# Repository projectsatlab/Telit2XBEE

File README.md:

# Telit2XBEE
XBEE form factor for Telit Sigfox and ZigBee module

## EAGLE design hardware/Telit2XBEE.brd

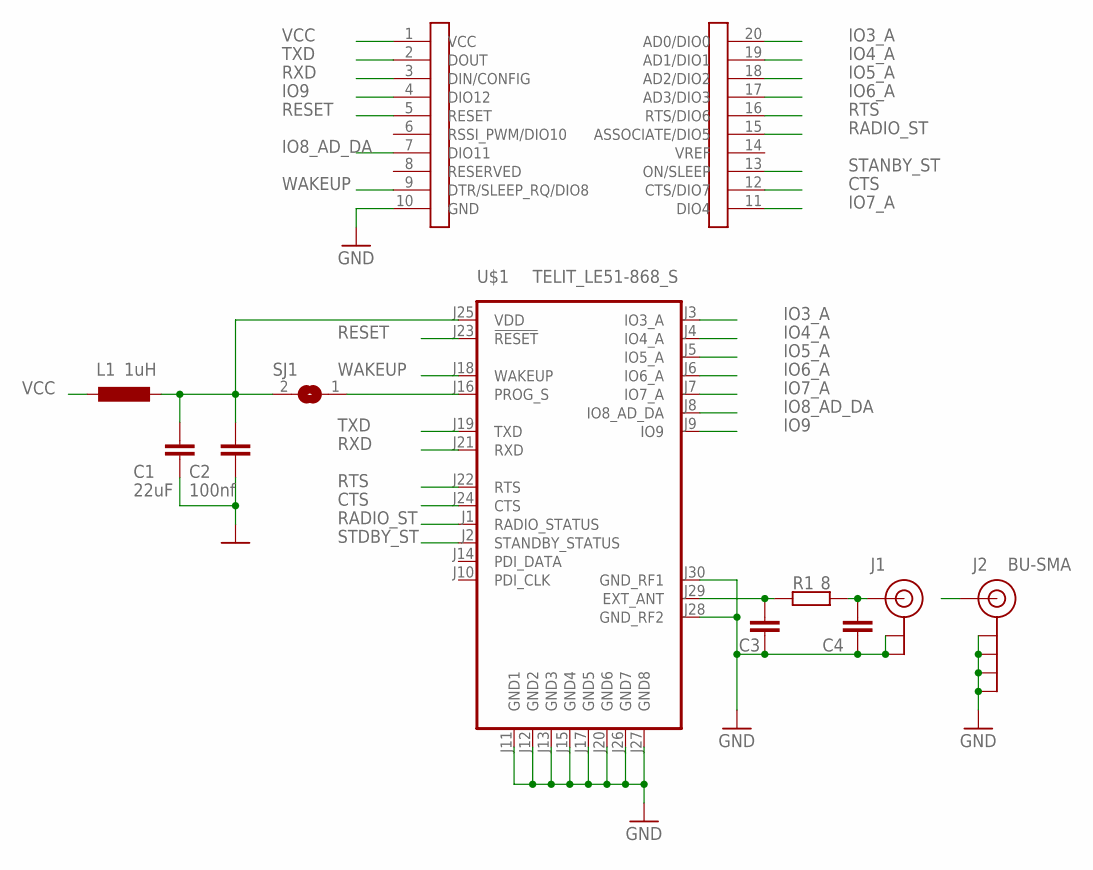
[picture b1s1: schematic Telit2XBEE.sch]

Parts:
C1: 22uF; C1206
C2: 100nf; C0805
C3, C4: C-EUC0201; C0201
J1: U.FL; U.FL_1PAD
J2: BU-SMA; BU-SMA-G
L1: 1uH; COILCRAFT_LPS3015
R1: 8; R0201
SJ1: SJ
U$1: TELIT_LE51-868_S; TELIT_LE51
U$2: XBEE_PIN_HEADER

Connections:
CTS: U$1.J24 (CTS), U$2.12 (CTS/DIO7)
GND: C1.2, C2.2, C3.2, C4.2, J1.P$1 (GND), J1.P$2 (GND), J2.P$2 (GND), J2.P$3 (GND), J2.P$5 (GND), J2.P$6 (GND), U$1.J11 (GND1), U$1.J12 (GND2), U$1.J13 (GND3), U$1.J15 (GND4), U$1.J17 (GND5), U$1.J20 (GND6), U$1.J26 (GND7), U$1.J27 (GND8), U$1.J28 (GND_RF2), U$1.J30 (GND_RF1), U$2.10 (GND)
IO3_A: U$1.J3 (IO3_A), U$2.20 (AD0/DIO0)
IO4_A: U$1.J4 (IO4_A), U$2.19 (AD1/DIO1)
IO5_A: U$1.J5 (IO5_A), U$2.18 (AD2/DIO2)
IO6_A: U$1.J6 (IO6_A), U$2.17 (AD3/DIO3)
IO7_A: U$1.J7 (IO7_A), U$2.11 (DIO4)
IO8_AD_DA: U$1.J8 (IO8_AD_DA), U$2.7 (DIO11)
IO9: U$1.J9 (IO9), U$2.4 (DIO12)
unnamed: SJ1.1, U$1.J16 (PROG_S)
unnamed: C4.1, J1.P$3 (SIGNAL), J2.P$1 (SIGNAL), R1.2
unnamed: C3.1, R1.1, U$1.J29 (EXT_ANT)
unnamed: C1.1, C2.1, L1.P$2 (2), SJ1.2, U$1.J25 (VDD)
RADIO_ST: U$1.J1 (RADIO_STATUS), U$2.15 (ASSOCIATE/DIO5)
RESET: U$1.J23 (!RESET), U$2.5 (RESET)
RTS: U$1.J22 (RTS), U$2.16 (RTS/DIO6)
RXD: U$1.J21 (RXD), U$2.3 (DIN/CONFIG)
STANBY_ST: U$2.13 (ON/SLEEP)
STDBY_ST: U$1.J2 (STANDBY_STATUS)
TXD: U$1.J19 (TXD), U$2.2 (DOUT)
VCC: L1.P$1 (1), U$2.1 (VCC)
WAKEUP: U$1.J18 (WAKEUP), U$2.9 (DTR/SLEEP_RQ/DIO8)

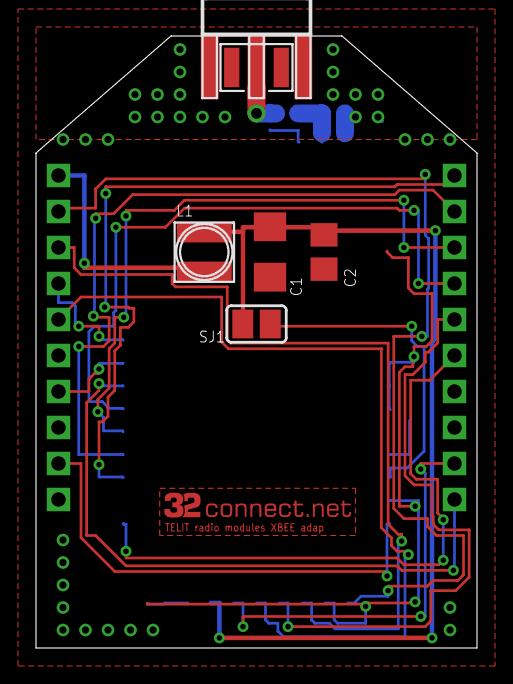
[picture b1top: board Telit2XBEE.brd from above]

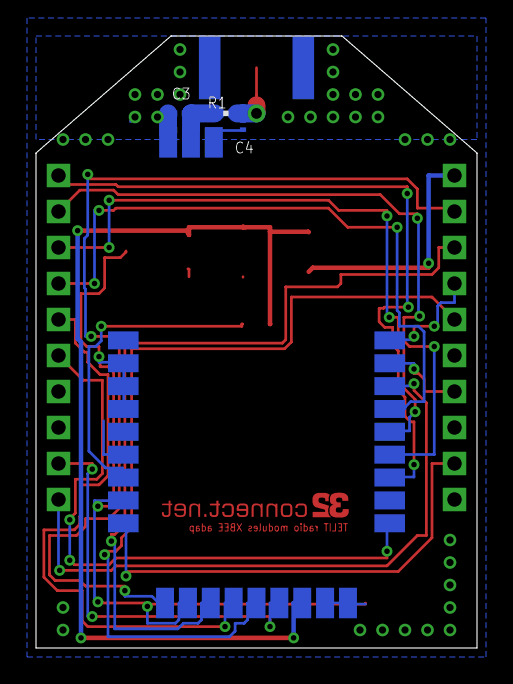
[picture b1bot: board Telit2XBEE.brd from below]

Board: 2 copper layers, 24.5 x 34.0 mm, 11 parts (4 on the bottom side), 20 nets.
